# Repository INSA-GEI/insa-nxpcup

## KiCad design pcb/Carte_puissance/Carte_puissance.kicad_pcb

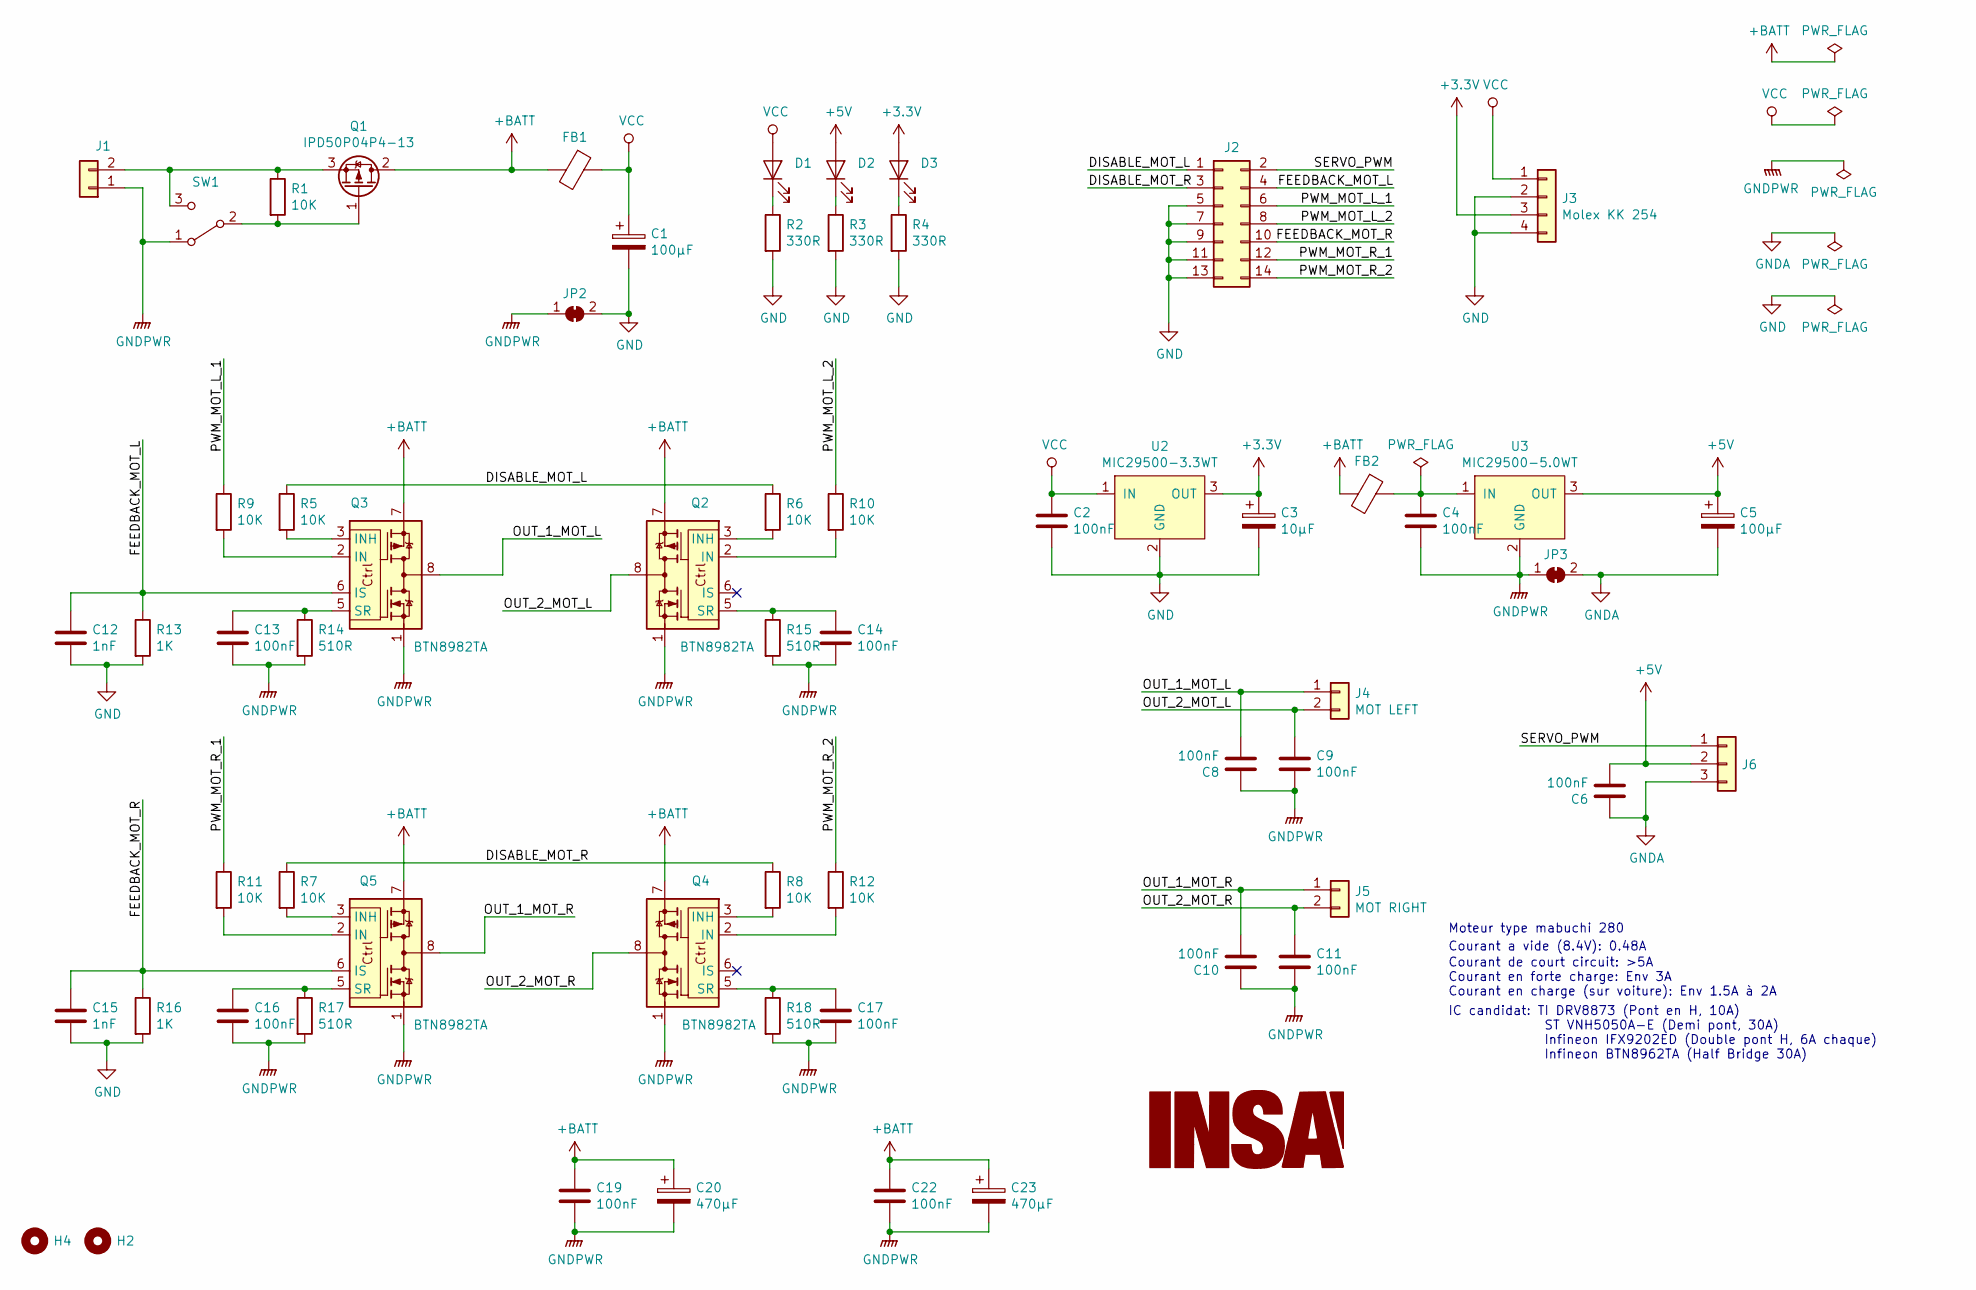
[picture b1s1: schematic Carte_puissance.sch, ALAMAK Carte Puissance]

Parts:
C1, C5: 100µF; CP_Radial_D6.3mm_P2.50mm
C2, C4, C6, C8, C9, C10, C11, C13, C14, C16, C17, C19, C22: 100nF; C_1206_3216Metric_Pad1.42x1.75mm_HandSolder
C3: 10µF; CP_Radial_D5.0mm_P2.00mm
C12, C15: 1nF; C_1206_3216Metric_Pad1.42x1.75mm_HandSolder
C20, C23: 470µF; CP_Radial_D6.3mm_P2.50mm
D1, D2, D3: LED; LED_D3.0mm
FB1, FB2: Ferrite_Bead; C_1812_4532Metric_Pad1.30x3.40mm_HandSolder
H2, H4: MountingHole; MountingHole_3.2mm_M3
J1: Conn_01x02; SolderWirePad_1x02_P7.62mm_Drill2mm
J2: Conn_02x07_Odd_Even; Multicomp_MC9A12-1434_2x07_P2.54mm_Vertical
J3: Molex KK 254; Molex_KK-254_AE-6410-04A_1x04_P2.54mm_Vertical
J4: MOT LEFT; JST_VH_B2PS-VH_1x02_P3.96mm_Horizontal
J5: MOT RIGHT; JST_VH_B2PS-VH_1x02_P3.96mm_Horizontal
J6: Conn_01x03; SolderWirePad_1x03_P3.175mm_Drill1mm
JP2, JP3: SolderJumper_2_Bridged; SolderJumper-2_P1.3mm_Bridged2Bar_RoundedPad1.0x1.5mm
Q1: IPD50P04P4-13; TO-252-2
Q2, Q3, Q4, Q5: BTN8982TA; TO-263-7_TabPin8
R1, R5, R6, R7, R8, R9, R10, R11, R12: 10K; R_1206_3216Metric_Pad1.42x1.75mm_HandSolder
R2, R3, R4: 330R; R_1206_3216Metric_Pad1.42x1.75mm_HandSolder
R13, R16: 1K; R_1206_3216Metric_Pad1.42x1.75mm_HandSolder
R14, R15, R17, R18: 510R; R_1206_3216Metric_Pad1.42x1.75mm_HandSolder
SW1: SW_SPDT; SW_Slide_1P2T_CK_OS102011MS2Q
U2: MIC29500-3.3WT; TO-220-3_Horizontal_TabDown
U3: MIC29500-5.0WT; TO-220-3_Horizontal_TabDown

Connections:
+3V3: C3.1, D3.2 (A), J3.3, U2.3 (OUT)
+5V: C5.1, C6.2, D2.2 (A), J6.2, U3.3 (OUT)
+BATT: C19.1, C20.1, C22.1, C23.1, FB1.2, FB2.2, Q1.2 (D), Q2.7, Q3.7, Q4.7, Q5.7
/DISABLE_MOT_L: J2.1, R5.1, R6.1
/DISABLE_MOT_R: J2.3, R7.1, R8.1
/FEEDBACK_MOT_L: C12.1, J2.4, Q3.6 (IS), R13.1
/FEEDBACK_MOT_R: C15.1, J2.10, Q5.6 (IS), R16.1
/OUT_1_MOT_L: C8.2, J4.1, Q3.4, Q3.8
/OUT_1_MOT_R: C10.2, J5.1, Q5.4, Q5.8
/OUT_2_MOT_L: C9.1, J4.2, Q2.4, Q2.8
/OUT_2_MOT_R: C11.1, J5.2, Q4.4, Q4.8
/PWM_MOT_L_1: J2.6, R9.1
/PWM_MOT_L_2: J2.8, R10.1
/PWM_MOT_R_1: J2.12, R11.1
/PWM_MOT_R_2: J2.14, R12.1
/SERVO_PWM: J2.2, J6.1
GND: C1.2, C2.2, C3.2, C12.2, C15.2, J2.5, J2.7, J2.9, J2.11, J2.13, J3.2, J3.4, JP2.2 (B), R2.2, R3.2, R4.2, R13.2, R16.2, U2.2 (GND)
GNDA: C5.2, C6.1, J6.3, JP3.2 (B)
GNDPWR: C4.2, C8.1, C9.2, C10.1, C11.2, C13.2, C14.2, C16.2, C17.2, C19.2, C20.2, C22.2, C23.2, J1.1, JP2.1 (A), JP3.1 (A), Q2.1, Q3.1, Q4.1, Q5.1, R14.2, R15.2, R17.2, R18.2, SW1.1 (A), U3.2 (GND)
unnamed: C4.1, FB2.1, U3.1 (IN)
unnamed: C13.1, Q3.5 (SR), R14.1
unnamed: C14.1, Q2.5 (SR), R15.1
unnamed: C16.1, Q5.5 (SR), R17.1
unnamed: C17.1, Q4.5 (SR), R18.1
unnamed: D1.1 (K), R2.1
unnamed: D2.1 (K), R3.1
unnamed: D3.1 (K), R4.1
unnamed: J1.2, Q1.3 (S), R1.1, SW1.3 (C)
unnamed: Q1.1 (G), R1.2, SW1.2 (B)
unnamed: Q2.2 (IN), R10.2
unnamed: Q2.3 (INH), R6.2
unnamed: Q3.2 (IN), R9.2
unnamed: Q3.3 (INH), R5.2
unnamed: Q4.2 (IN), R12.2
unnamed: Q4.3 (INH), R8.2
unnamed: Q5.2 (IN), R11.2
unnamed: Q5.3 (INH), R7.2
VCC: C1.1, C2.1, D1.2 (A), FB1.1, J3.1, U2.1 (IN)

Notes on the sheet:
Moteur type mabuchi 280
Courant a vide (8.4V): 0.48A
Courant de court circuit: >5A Courant en forte charge: Env 3A Courant en charge (sur voiture): Env 1.5A à 2A
IC candidat: TI DRV8873 (Pont en H, 10A) ST VNH5050A-E (Demi pont, 30A) Infineon IFX9202ED (Double pont H, 6A chaque) Infineon BTN8962TA (Half Bridge 30A)

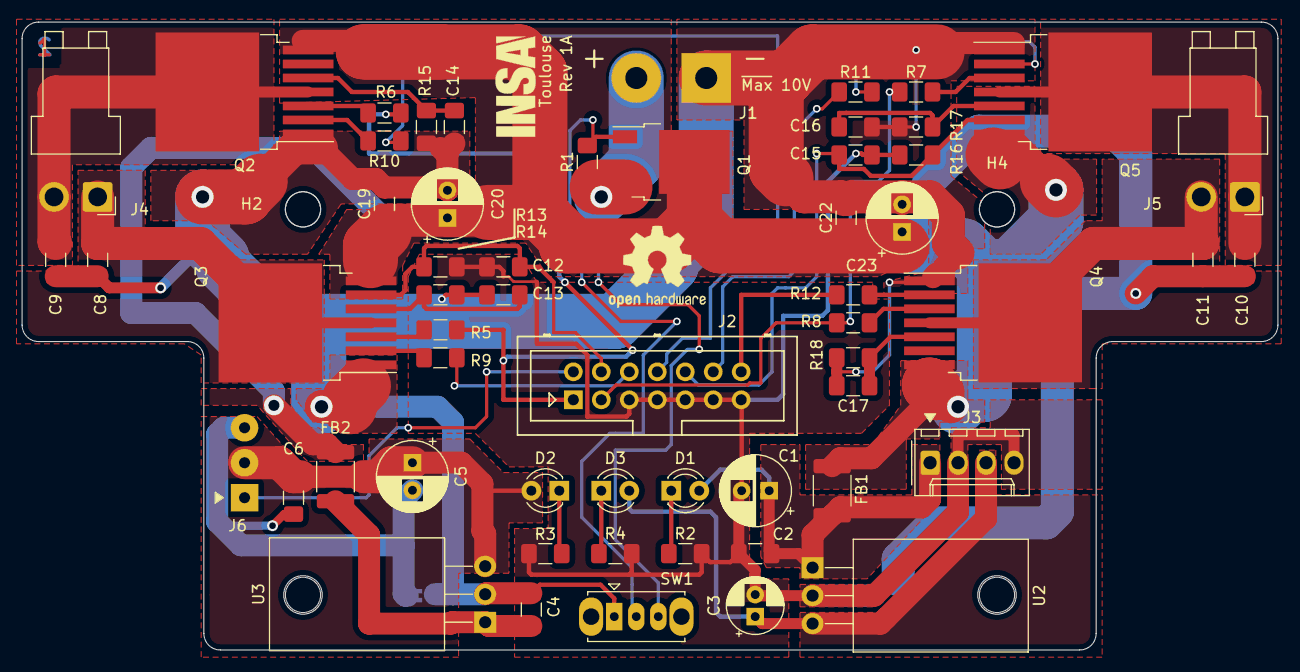
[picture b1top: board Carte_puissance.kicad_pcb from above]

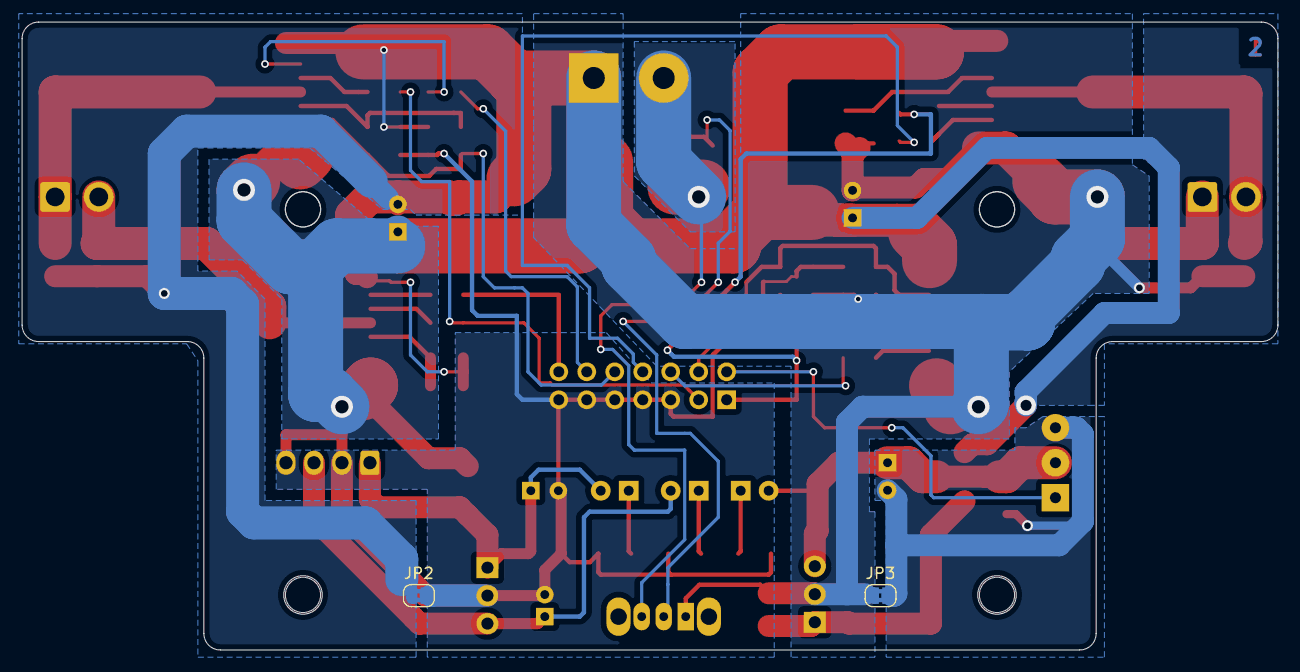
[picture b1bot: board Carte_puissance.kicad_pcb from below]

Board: 2 copper layers, 114.0 x 57.0 mm, 63 parts (2 on the bottom side), 38 nets.

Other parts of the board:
REF1: OSHW-Logo2_9.8x8mm_SilkScreen
REF2: LOGO; insa-image

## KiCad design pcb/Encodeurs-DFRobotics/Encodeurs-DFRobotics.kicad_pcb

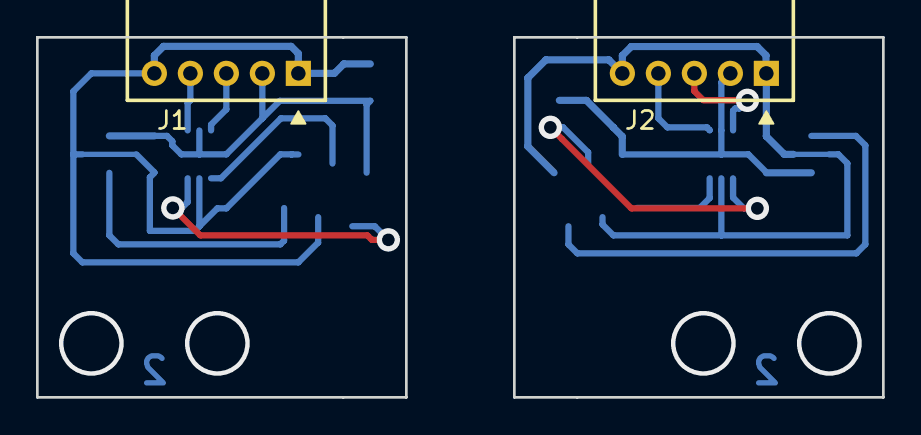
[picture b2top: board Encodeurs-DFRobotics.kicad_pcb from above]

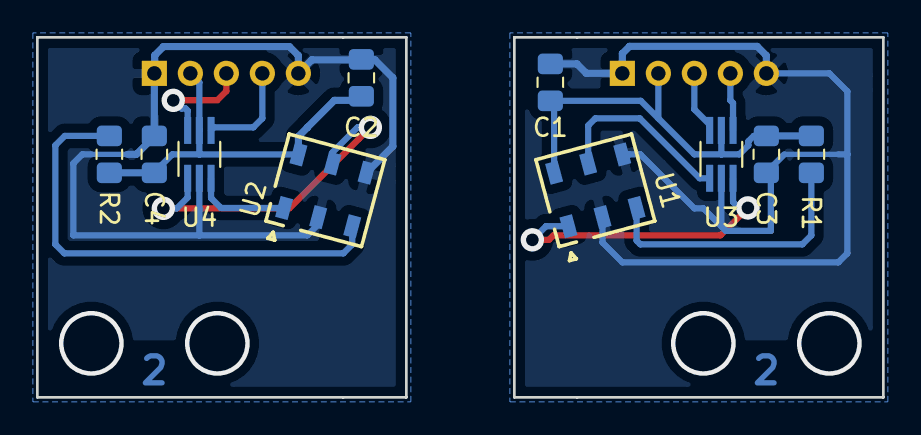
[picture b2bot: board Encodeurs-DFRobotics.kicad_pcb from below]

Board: 2 copper layers, 47.0 x 20.0 mm, 12 parts (10 on the bottom side), 12 nets.

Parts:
C1, C2: 1µF; C_0805_2012Metric_Pad1.15x1.40mm_HandSolder
C3, C4: 100nF; C_0805_2012Metric_Pad1.15x1.40mm_HandSolder
J1, J2: DF3A-5P-2DS
R1, R2: 200; R_0805_2012Metric_Pad1.15x1.40mm_HandSolder
U1, U2: AEDR-8300
U3, U4: 74LVC2G34; SOT-363_SC-70-6_Handsoldering

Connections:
+5V: C1.1, C2.1, C3.1, C4.1, J1.2, J2.2, R1.1, R2.1, U1.6, U2.6, U3.5, U4.5
/SENS_LEFT_A: J1.3, U3.6
/SENS_LEFT_B: J1.4, U3.4
/SENS_RIGHT_A: J2.3, U4.6
/SENS_RIGHT_B: J2.4, U4.4
GND: C1.2, C2.2, C3.2, C4.2, J1.1, J1.5, J2.1, J2.5, U1.2, U1.4, U2.2, U2.4, U3.2, U4.2
unnamed: R1.2, U1.3
unnamed: R2.2, U2.3
unnamed: U1.1, U3.3
unnamed: U1.5, U3.1
unnamed: U2.1, U4.3
unnamed: U2.5, U4.1
